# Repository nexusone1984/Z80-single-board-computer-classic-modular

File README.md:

# Z80-single-board-computer-classic-modular
CAD drawings and source code for projects using the Z80 single board computer

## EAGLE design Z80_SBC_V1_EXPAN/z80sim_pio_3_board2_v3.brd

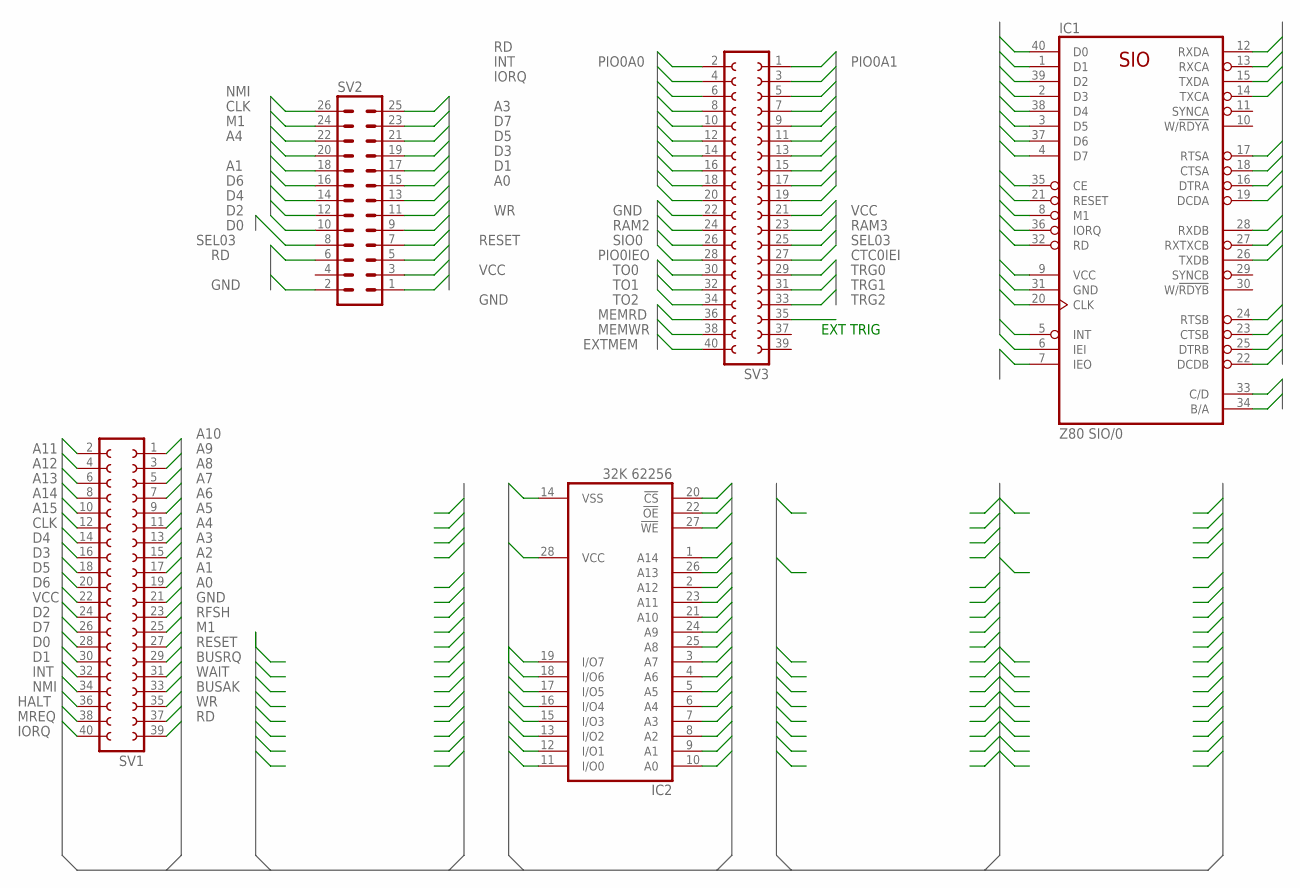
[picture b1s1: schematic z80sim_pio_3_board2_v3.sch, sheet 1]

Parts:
IC1: Z80 SIO/0; DIL40
IC2: 32K 62256; DIL28-6
SV1, SV3: FE20-2
SV2: MA13-2

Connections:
32K_SEL: IC2.20 (!CS); also elsewhere on the board
A0: IC1.34 (B/A), IC2.10 (A0), SV1.21, SV2.9
A1: IC1.33 (C/D), IC2.9 (A1), SV1.19, SV2.18
A2: IC2.8 (A2), SV1.17
A3: IC2.7 (A3), SV1.15, SV2.19
A4: IC2.6 (A4), SV1.13, SV2.20
A5: IC2.5 (A5), SV1.11
A6: IC2.4 (A6), SV1.9
A7: IC2.3 (A7), SV1.7
A8: IC2.25 (A8), SV1.5
A9: IC2.24 (A9), SV1.3
A10: IC2.21 (A10), SV1.1
A11: IC2.23 (A11), SV1.2
A12: IC2.2 (A12), SV1.4
A13: IC2.26 (A13), SV1.6
A14: IC2.1 (A14), SV1.8
A15: SV1.10
BUSAK: SV1.35
BUSRQ: SV1.31
CLK: IC1.20 (CLK), SV1.12, SV2.24
CTC0IEI: IC1.7 (IEO), SV3.27; also elsewhere on the board
CTSA: IC1.18 (CTSA)
CTSB: IC1.23 (CTSB)
D0: IC1.40 (D0), IC2.11 (I/O0), SV1.28, SV2.10
D1: IC1.1 (D1), IC2.12 (I/O1), SV1.30, SV2.11
D2: IC1.39 (D2), IC2.13 (I/O2), SV1.24, SV2.12
D3: IC1.2 (D3), IC2.15 (I/O3), SV1.16, SV2.13
D4: IC1.38 (D4), IC2.16 (I/O4), SV1.14, SV2.14
D5: IC1.3 (D5), IC2.17 (I/O5), SV1.18, SV2.15
D6: IC1.37 (D6), IC2.18 (I/O6), SV1.20, SV2.16
D7: IC1.4 (D7), IC2.19 (I/O7), SV1.26, SV2.17
DCDA: IC1.19 (DCDA)
DCDB: IC1.22 (DCDB)
DTRA: IC1.16 (DTRA)
DTRB: IC1.25 (DTRB)
EXTMEM: SV3.40
GND: IC1.31 (GND), IC2.14 (VSS), SV1.23, SV2.1, SV2.2, SV3.22; also elsewhere on the board
HALT: SV1.36
INT: IC1.5 (INT), SV1.32, SV2.23
IORQ: IC1.36 (IORQ), SV1.40, SV2.21; also elsewhere on the board
M1: IC1.8 (M1), SV1.27, SV2.22
MEMRD: IC2.22 (!OE), SV3.36
MEMWR: IC2.27 (!WE), SV3.38
MREQ: SV1.38
NMI: SV1.34, SV2.26
PIO0A0: SV3.2
PIO0A1: SV3.1
PIO0A2: SV3.4
PIO0A3: SV3.3
PIO0A4: SV3.6
PIO0A5: SV3.5
PIO0A6: SV3.8
PIO0A7: SV3.7
PIO0ARDY: SV3.10
PIO0ASTB: SV3.9
PIO0B0: SV3.12
PIO0B1: SV3.11
PIO0B2: SV3.14
PIO0B3: SV3.13
PIO0B4: SV3.16
PIO0B5: SV3.15
PIO0B6: SV3.18
PIO0B7: SV3.17
PIO0BRDY: SV3.20
PIO0BSTB: SV3.19
PIO0IEO: SV3.28
RAM2: SV3.24
RAM3: SV3.23
RD: IC1.32 (RD), SV1.39, SV2.6, SV2.25
RESET: IC1.21 (RESET), SV1.29, SV2.5
RFSH: SV1.25
RTSA: IC1.17 (RTSA)
RTSB: IC1.24 (RTSB)
RXCA: IC1.13 (RXCA)
RXDA: IC1.12 (RXDA)
RXDB: IC1.28 (RXDB)
RXTXCB: IC1.27 (RXTXCB)
SEL03: SV2.8, SV3.25
SIO0: IC1.35 (CE), SV3.26
TO0: SV3.30
TO1: SV3.32
TO2: SV3.34
TRG0: SV3.29
TRG1: SV3.31
TRG2: SV3.33
TXCA: IC1.14 (TXCA)
TXDA: IC1.15 (TXDA)
TXDB: IC1.26 (TXDB)
VCC: IC1.6 (IEI), IC1.9 (VCC), IC2.28 (VCC), SV1.22, SV2.3, SV3.21; also elsewhere on the board
WAIT: SV1.33
WR: SV1.37, SV2.7

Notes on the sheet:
EXT TRIG

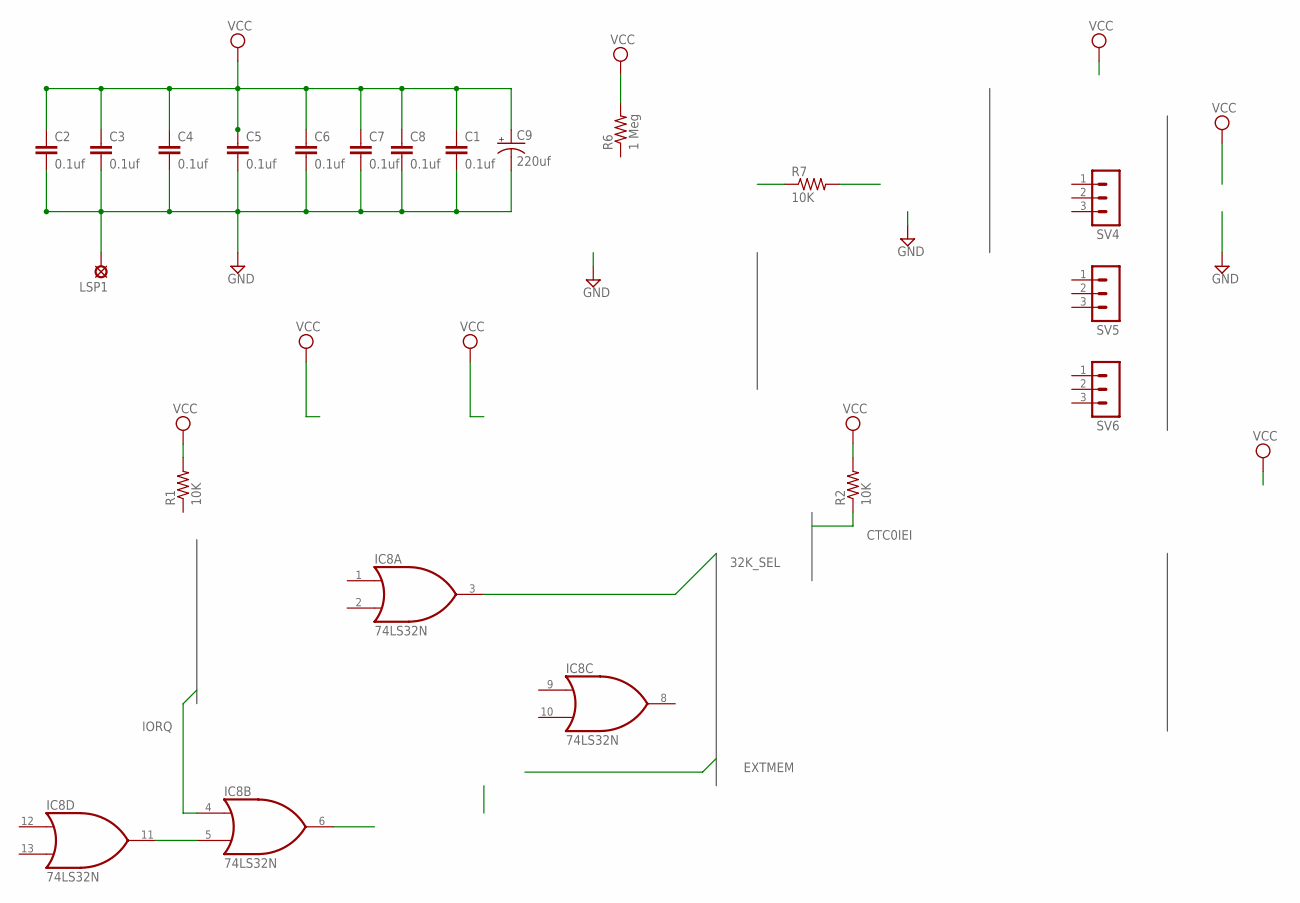
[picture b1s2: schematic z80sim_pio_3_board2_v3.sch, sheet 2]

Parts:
C1, C2, C3, C4, C5, C6, C7, C8: 0.1uf; C5B3
C9: 220uf; E3,5-10
IC8: 74LS32N; DIL14
LSP1: LSP13
R1, R2, R7: 10K; 0204/7
R6: 1 Meg; 0204/7
SV4, SV5, SV6: MA03-1

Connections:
32K_SEL: IC8.3 (O); also elsewhere on the board
CTC0IEI: R2.1; also elsewhere on the board
GND: C1.2, C2.2, C3.2, C4.2, C5.2, C6.2, C7.2, C8.2, C9.-, IC8.7 (GND), LSP1.MP; also elsewhere on the board
IORQ: IC8.4 (I0); also elsewhere on the board
unnamed: IC8.5 (I1), IC8.11 (O)
VCC: C1.1, C2.1, C3.1, C4.1, C5.1, C6.1, C7.1, C8.1, C9.+, IC8.14 (VCC), R1.2, R2.2, R6.2; also elsewhere on the board

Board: 2 copper layers, 23 parts (0 on the bottom side), 40 nets, no tracks yet.

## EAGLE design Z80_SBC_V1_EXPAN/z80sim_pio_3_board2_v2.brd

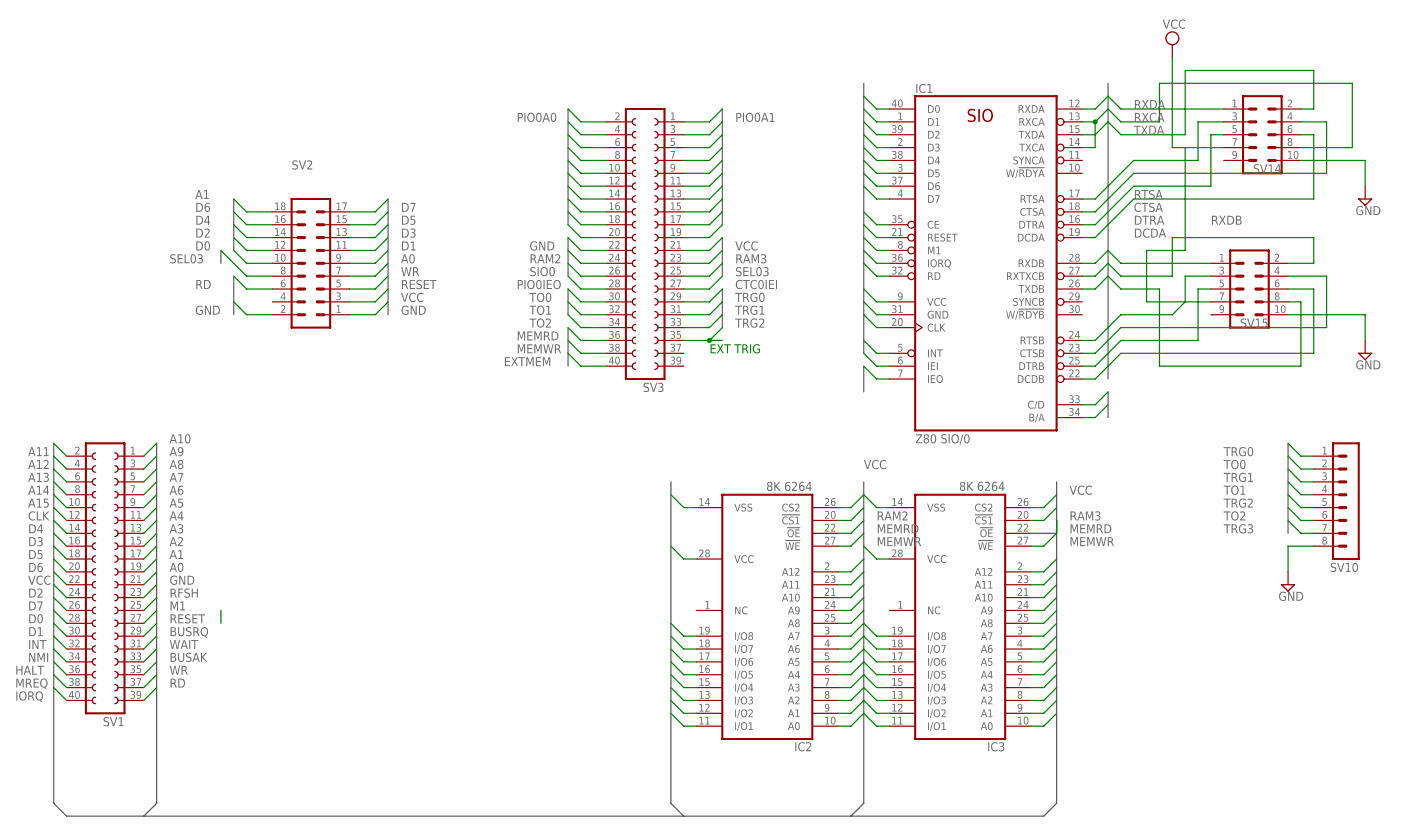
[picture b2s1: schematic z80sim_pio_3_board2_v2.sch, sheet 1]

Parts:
IC1: Z80 SIO/0; DIL40
IC2, IC3: 8K 6264; DIL28-6
SV1, SV3: FE20-2
SV2: MA09-2
SV10: MA08-1
SV14, SV15: MA05-2

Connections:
A0: IC1.34 (B/A), IC2.10 (A0), IC3.10 (A0), SV1.21, SV2.9
A1: IC1.33 (C/D), IC2.9 (A1), IC3.9 (A1), SV1.19, SV2.18
A2: IC2.8 (A2), IC3.8 (A2), SV1.17
A3: IC2.7 (A3), IC3.7 (A3), SV1.15
A4: IC2.6 (A4), IC3.6 (A4), SV1.13
A5: IC2.5 (A5), IC3.5 (A5), SV1.11
A6: IC2.4 (A6), IC3.4 (A6), SV1.9
A7: IC2.3 (A7), IC3.3 (A7), SV1.7
A8: IC2.25 (A8), IC3.25 (A8), SV1.5
A9: IC2.24 (A9), IC3.24 (A9), SV1.3
A10: IC2.21 (A10), IC3.21 (A10), SV1.1
A11: IC2.23 (A11), IC3.23 (A11), SV1.2
A12: IC2.2 (A12), IC3.2 (A12), SV1.4
A13: SV1.6
A14: SV1.8
A15: SV1.10
BUSAK: SV1.35
BUSRQ: SV1.31
CLK: IC1.20 (CLK), SV1.12
CTC0IEI: IC1.7 (IEO), SV3.27; also elsewhere on the board
CTSA: IC1.18 (CTSA), SV14.4
CTSB: IC1.23 (CTSB), SV15.4
D0: IC1.40 (D0), IC2.11 (I/O1), IC3.11 (I/O1), SV1.28, SV2.10
D1: IC1.1 (D1), IC2.12 (I/O2), IC3.12 (I/O2), SV1.30, SV2.11
D2: IC1.39 (D2), IC2.13 (I/O3), IC3.13 (I/O3), SV1.24, SV2.12
D3: IC1.2 (D3), IC2.15 (I/O4), IC3.15 (I/O4), SV1.16, SV2.13
D4: IC1.38 (D4), IC2.16 (I/O5), IC3.16 (I/O5), SV1.14, SV2.14
D5: IC1.3 (D5), IC2.17 (I/O6), IC3.17 (I/O6), SV1.18, SV2.15
D6: IC1.37 (D6), IC2.18 (I/O7), IC3.18 (I/O7), SV1.20, SV2.16
D7: IC1.4 (D7), IC2.19 (I/O8), IC3.19 (I/O8), SV1.26, SV2.17
DCDA: IC1.19 (DCDA), SV14.6
DCDB: IC1.22 (DCDB), SV15.6
DTRA: IC1.16 (DTRA), SV14.5
DTRB: IC1.25 (DTRB), SV15.5
EXTMEM: SV3.40
GND: IC1.31 (GND), IC2.14 (VSS), IC3.14 (VSS), SV1.23, SV2.1, SV2.2, SV3.22, SV10.8, SV14.10, SV15.10; also elsewhere on the board
HALT: SV1.36
INT: IC1.5 (INT), SV1.32
IORQ: IC1.36 (IORQ), SV1.40
M1: IC1.8 (M1), SV1.27
MEMRD: IC2.22 (!OE), IC3.22 (!OE), SV3.36
MEMWR: IC2.27 (!WE), IC3.27 (!WE), SV3.38
MREQ: SV1.38
NMI: SV1.34
PIO0A0: SV3.2; also elsewhere on the board
PIO0A1: SV3.1; also elsewhere on the board
PIO0A2: SV3.4; also elsewhere on the board
PIO0A3: SV3.3; also elsewhere on the board
PIO0A4: SV3.6; also elsewhere on the board
PIO0A5: SV3.5; also elsewhere on the board
PIO0A6: SV3.8; also elsewhere on the board
PIO0A7: SV3.7; also elsewhere on the board
PIO0ARDY: SV3.10; also elsewhere on the board
PIO0ASTB: SV3.9; also elsewhere on the board
PIO0B0: SV3.12; also elsewhere on the board
PIO0B1: SV3.11; also elsewhere on the board
PIO0B2: SV3.14; also elsewhere on the board
PIO0B3: SV3.13; also elsewhere on the board
PIO0B4: SV3.16; also elsewhere on the board
PIO0B5: SV3.15; also elsewhere on the board
PIO0B6: SV3.18; also elsewhere on the board
PIO0B7: SV3.17; also elsewhere on the board
PIO0BRDY: SV3.20; also elsewhere on the board
PIO0BSTB: SV3.19; also elsewhere on the board
PIO0IEO: SV3.28
RAM2: IC2.20 (!CS1), SV3.24
RAM3: IC3.20 (!CS1), SV3.23
RD: IC1.32 (RD), SV1.39, SV2.6
RESET: IC1.21 (RESET), SV1.29, SV2.5
RFSH: SV1.25
RTSA: IC1.17 (RTSA), SV14.3
RTSB: IC1.24 (RTSB), SV15.3
RXCA: IC1.13 (RXCA), IC1.14 (TXCA), SV14.8; also elsewhere on the board
RXDA: IC1.12 (RXDA), SV14.1
RXDB: IC1.28 (RXDB), SV15.1
RXTXCB: IC1.27 (RXTXCB), SV15.8; also elsewhere on the board
SEL03: SV2.8, SV3.25
SIO0: IC1.35 (CE), SV3.26
TO0: SV3.30, SV10.2; also elsewhere on the board
TO1: SV3.32, SV10.4; also elsewhere on the board
TO2: SV3.34, SV10.6
TRG0: SV3.29, SV10.1
TRG1: SV3.31, SV10.3
TRG2: SV3.33, SV10.5
TRG3: SV3.35, SV10.7
TXDA: IC1.15 (TXDA), SV14.2
TXDB: IC1.26 (TXDB), SV15.2
VCC: IC1.6 (IEI), IC1.9 (VCC), IC2.26 (CS2), IC2.28 (VCC), IC3.26 (CS2), IC3.28 (VCC), SV1.22, SV2.3, SV3.21, SV14.7, SV15.7; also elsewhere on the board
WAIT: SV1.33
WR: SV1.37, SV2.7

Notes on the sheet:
EXT TRIG

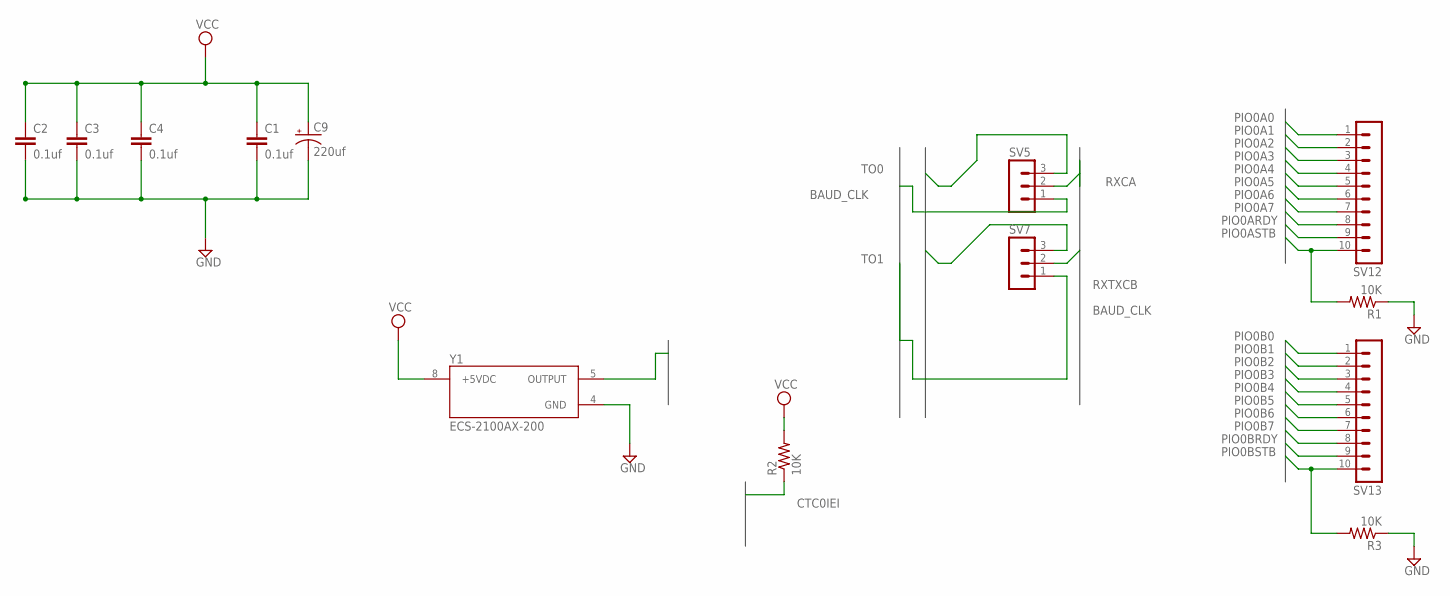
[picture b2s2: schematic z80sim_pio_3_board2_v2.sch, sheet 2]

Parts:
C1, C2, C3, C4: 0.1uf; C5B3
C9: 220uf; E3,5-10
R1, R2, R3: 10K; 0204/7
SV5, SV7: MA03-1
SV12, SV13: MA10-1
Y1: ECS-2100AX-200

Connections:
BAUD_CLK: SV5.1, SV7.1, Y1.5 (OUTPUT)
CTC0IEI: R2.1; also elsewhere on the board
GND: C1.2, C2.2, C3.2, C4.2, C9.-, R1.1, R3.1, Y1.4 (GND); also elsewhere on the board
PIO0A0: SV12.1; also elsewhere on the board
PIO0A1: SV12.2; also elsewhere on the board
PIO0A2: SV12.3; also elsewhere on the board
PIO0A3: SV12.4; also elsewhere on the board
PIO0A4: SV12.5; also elsewhere on the board
PIO0A5: SV12.6; also elsewhere on the board
PIO0A6: SV12.7; also elsewhere on the board
PIO0A7: SV12.8; also elsewhere on the board
PIO0ARDY: SV12.9; also elsewhere on the board
PIO0ASTB: R1.2, SV12.10; also elsewhere on the board
PIO0B0: SV13.1; also elsewhere on the board
PIO0B1: SV13.2; also elsewhere on the board
PIO0B2: SV13.3; also elsewhere on the board
PIO0B3: SV13.4; also elsewhere on the board
PIO0B4: SV13.5; also elsewhere on the board
PIO0B5: SV13.6; also elsewhere on the board
PIO0B6: SV13.7; also elsewhere on the board
PIO0B7: SV13.8; also elsewhere on the board
PIO0BRDY: SV13.9; also elsewhere on the board
PIO0BSTB: R3.2, SV13.10; also elsewhere on the board
RXCA: SV5.2; also elsewhere on the board
RXTXCB: SV7.2; also elsewhere on the board
TO0: SV5.3; also elsewhere on the board
TO1: SV7.3; also elsewhere on the board
VCC: C1.1, C2.1, C3.1, C4.1, C9.+, R2.2, Y1.8 (+5VDC); also elsewhere on the board

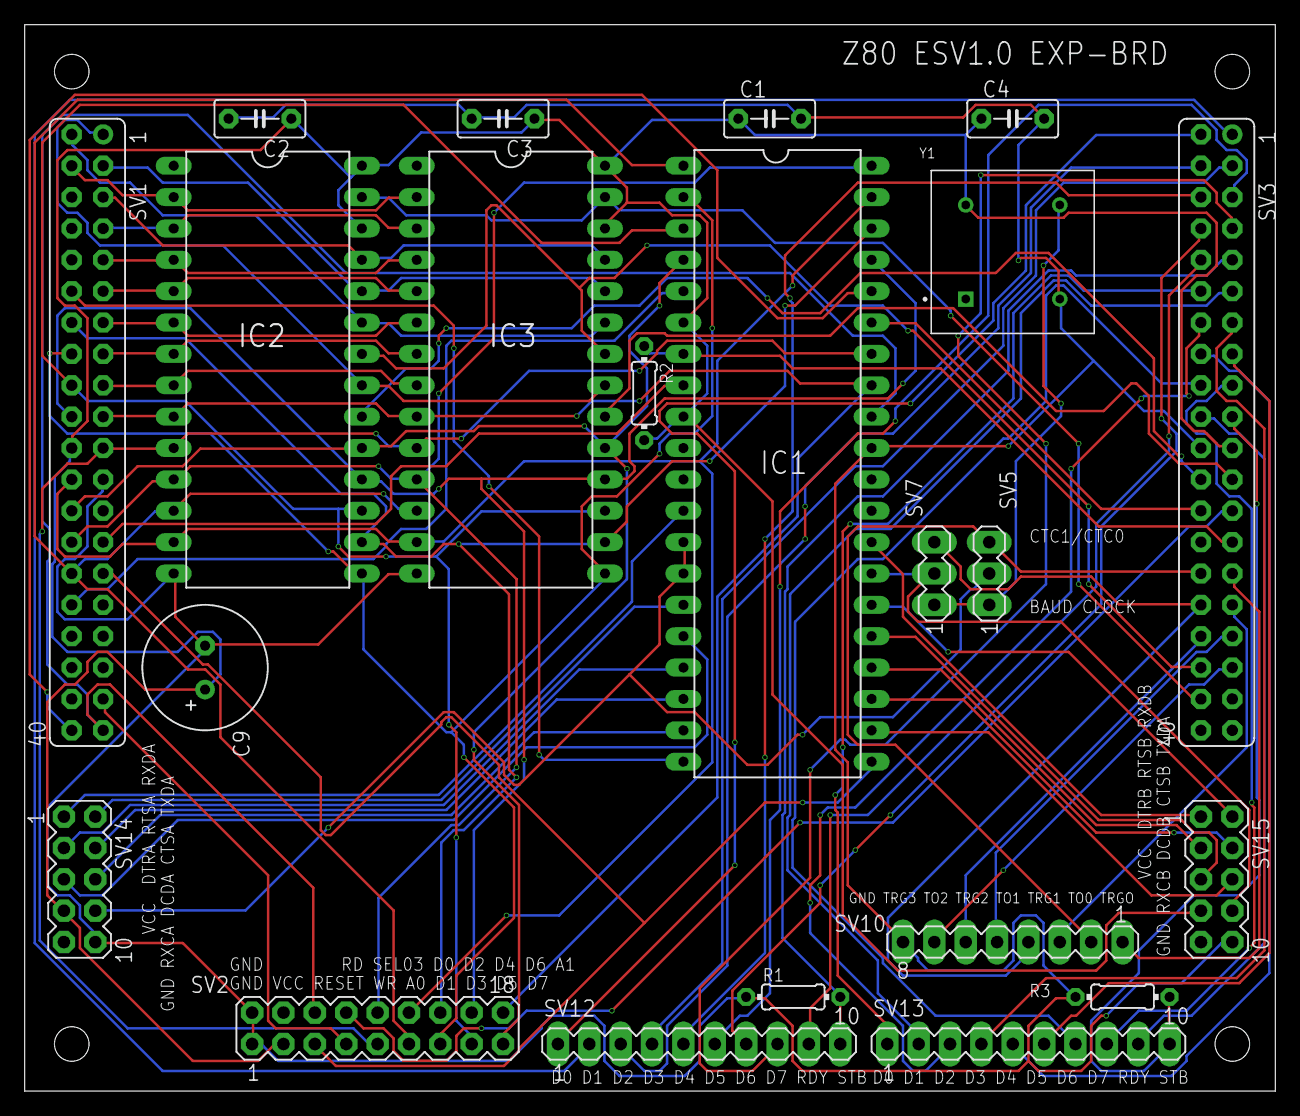
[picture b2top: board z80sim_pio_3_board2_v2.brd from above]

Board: 2 copper layers, 101.3 x 86.3 mm, 22 parts (0 on the bottom side), 79 nets.

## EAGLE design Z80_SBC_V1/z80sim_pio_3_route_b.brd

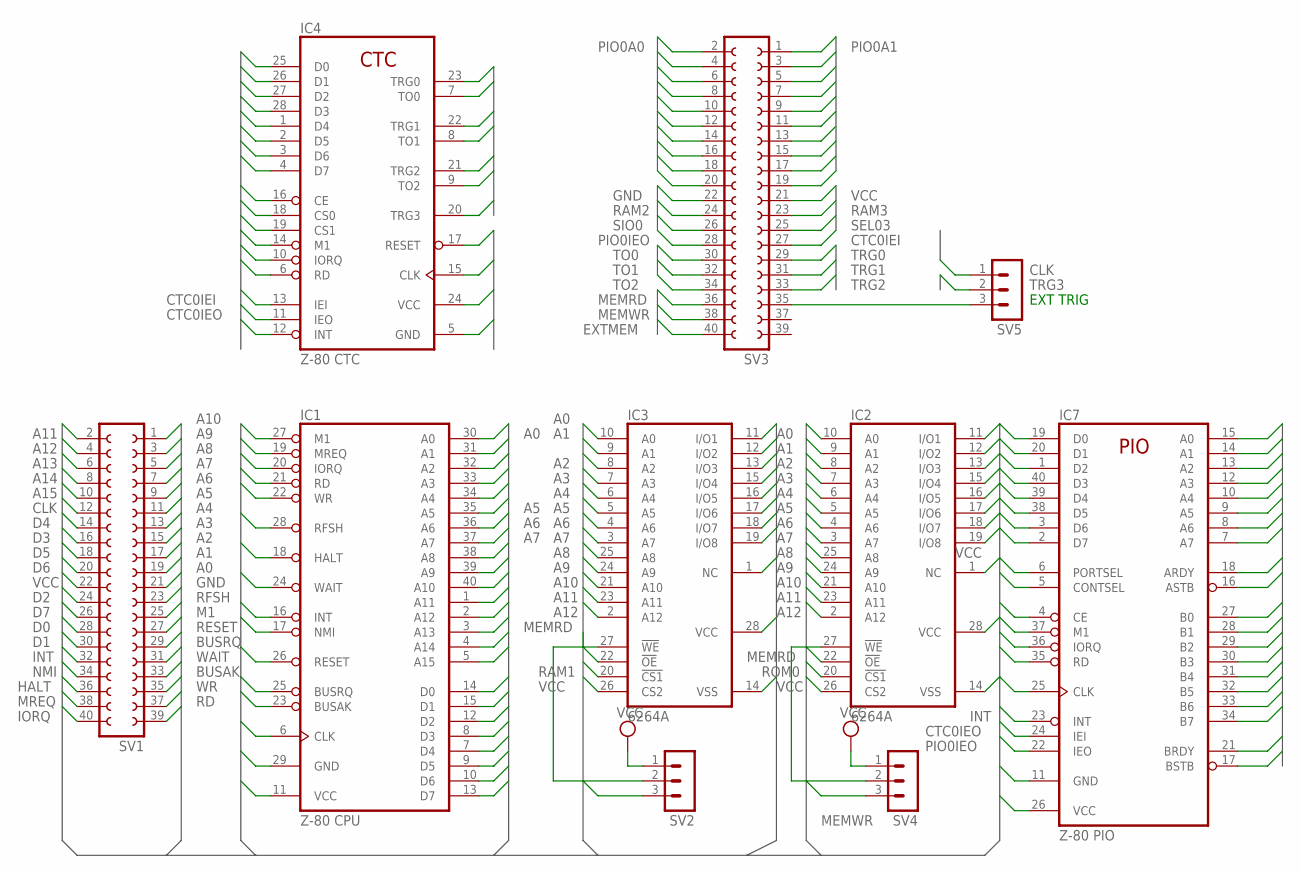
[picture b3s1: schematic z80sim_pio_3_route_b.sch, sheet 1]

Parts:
IC1: Z-80 CPU; DIL40
IC2, IC3: 6264A; DIL28-6
IC4: Z-80 CTC; DIL28
IC7: Z-80 PIO; DIL40
SV1, SV3: FE20-2
SV2, SV4, SV5: MA03-1

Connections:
A0: IC1.30 (A0), IC2.10 (A0), IC3.10 (A0), IC4.18 (CS0), IC7.6 (PORTSEL), SV1.21
A1: IC1.31 (A1), IC2.9 (A1), IC3.9 (A1), IC4.19 (CS1), IC7.5 (CONTSEL), SV1.19
A2: IC1.32 (A2), IC2.8 (A2), IC3.8 (A2), SV1.17
A3: IC1.33 (A3), IC2.7 (A3), IC3.7 (A3), SV1.15
A4: IC1.34 (A4), IC2.6 (A4), IC3.6 (A4), SV1.13
A5: IC1.35 (A5), IC2.5 (A5), IC3.5 (A5), SV1.11; also elsewhere on the board
A6: IC1.36 (A6), IC2.4 (A6), IC3.4 (A6), SV1.9; also elsewhere on the board
A7: IC1.37 (A7), IC2.3 (A7), IC3.3 (A7), SV1.7; also elsewhere on the board
A8: IC1.38 (A8), IC2.25 (A8), IC3.25 (A8), SV1.5
A9: IC1.39 (A9), IC2.24 (A9), IC3.24 (A9), SV1.3
A10: IC1.40 (A10), IC2.21 (A10), IC3.21 (A10), SV1.1
A11: IC1.1 (A11), IC2.23 (A11), IC3.23 (A11), SV1.2
A12: IC1.2 (A12), IC2.2 (A12), IC3.2 (A12), SV1.4
A13: IC1.3 (A13), SV1.6; also elsewhere on the board
A14: IC1.4 (A14), SV1.8; also elsewhere on the board
A15: IC1.5 (A15), SV1.10; also elsewhere on the board
BUSAK: IC1.23 (BUSAK), SV1.35
BUSRQ: IC1.25 (BUSRQ), SV1.31; also elsewhere on the board
CLK: IC1.6 (CLK), IC4.15 (CLK), IC7.25 (CLK), SV1.12, SV5.1; also elsewhere on the board
CTC0: IC4.16 (CE); also elsewhere on the board
CTC0IEI: IC4.13 (IEI), SV3.27; also elsewhere on the board
CTC0IEO: IC4.11 (IEO), IC7.24 (IEI)
D0: IC1.14 (D0), IC2.11 (I/O1), IC3.11 (I/O1), IC4.25 (D0), IC7.19 (D0), SV1.28
D1: IC1.15 (D1), IC2.12 (I/O2), IC3.12 (I/O2), IC4.26 (D1), IC7.20 (D1), SV1.30
D2: IC1.12 (D2), IC2.13 (I/O3), IC3.13 (I/O3), IC4.27 (D2), IC7.1 (D2), SV1.24
D3: IC1.8 (D3), IC2.15 (I/O4), IC3.15 (I/O4), IC4.28 (D3), IC7.40 (D3), SV1.16
D4: IC1.7 (D4), IC2.16 (I/O5), IC3.16 (I/O5), IC4.1 (D4), IC7.39 (D4), SV1.14
D5: IC1.9 (D5), IC2.17 (I/O6), IC3.17 (I/O6), IC4.2 (D5), IC7.38 (D5), SV1.18
D6: IC1.10 (D6), IC2.18 (I/O7), IC3.18 (I/O7), IC4.3 (D6), IC7.3 (D6), SV1.20
D7: IC1.13 (D7), IC2.19 (I/O8), IC3.19 (I/O8), IC4.4 (D7), IC7.2 (D7), SV1.26
EXTMEM: SV3.40; also elsewhere on the board
GND: IC1.29 (GND), IC2.14 (VSS), IC3.14 (VSS), IC4.5 (GND), IC7.11 (GND), SV1.23, SV3.22; also elsewhere on the board
HALT: IC1.18 (HALT), SV1.36
INT: IC1.16 (INT), IC4.12 (INT), IC7.23 (INT), SV1.32; also elsewhere on the board
IORQ: IC1.20 (IORQ), IC4.10 (IORQ), IC7.36 (IORQ), SV1.40; also elsewhere on the board
M1: IC1.27 (M1), IC4.14 (M1), IC7.37 (M1), SV1.27
MEMRD: IC2.22 (!OE), IC3.22 (!OE), SV3.36; also elsewhere on the board
MEMWR: SV2.3, SV3.38, SV4.3; also elsewhere on the board
MREQ: IC1.19 (MREQ), SV1.38; also elsewhere on the board
unnamed: IC2.27 (!WE), SV4.2
unnamed: SV3.35, SV5.3
unnamed: IC3.27 (!WE), SV2.2
NMI: IC1.17 (NMI), SV1.34; also elsewhere on the board
PIO0: IC7.4 (CE); also elsewhere on the board
PIO0A0: IC7.15 (A0), SV3.2
PIO0A1: IC7.14 (A1), SV3.1
PIO0A2: IC7.13 (A2), SV3.4
PIO0A3: IC7.12 (A3), SV3.3
PIO0A4: IC7.10 (A4), SV3.6
PIO0A5: IC7.9 (A5), SV3.5
PIO0A6: IC7.8 (A6), SV3.8
PIO0A7: IC7.7 (A7), SV3.7
PIO0ARDY: IC7.18 (ARDY), SV3.10
PIO0ASTB: IC7.16 (ASTB), SV3.9
PIO0B0: IC7.27 (B0), SV3.12
PIO0B1: IC7.28 (B1), SV3.11
PIO0B2: IC7.29 (B2), SV3.14
PIO0B3: IC7.30 (B3), SV3.13
PIO0B4: IC7.31 (B4), SV3.16
PIO0B5: IC7.32 (B5), SV3.15
PIO0B6: IC7.33 (B6), SV3.18
PIO0B7: IC7.34 (B7), SV3.17
PIO0BRDY: IC7.21 (BRDY), SV3.20
PIO0BSTB: IC7.17 (BSTB), SV3.19
PIO0IEO: IC7.22 (IEO), SV3.28
RAM1: IC3.20 (!CS1); also elsewhere on the board
RAM2: SV3.24; also elsewhere on the board
RAM3: SV3.23; also elsewhere on the board
RD: IC1.21 (RD), IC4.6 (RD), IC7.35 (RD), SV1.39; also elsewhere on the board
RESET: IC1.26 (RESET), IC4.17 (RESET), SV1.29; also elsewhere on the board
RFSH: IC1.28 (RFSH), SV1.25
ROM0: IC2.20 (!CS1); also elsewhere on the board
SEL03: SV3.25; also elsewhere on the board
SIO0: SV3.26; also elsewhere on the board
TO0: IC4.7 (TO0), SV3.30
TO1: IC4.8 (TO1), SV3.32
TO2: IC4.9 (TO2), SV3.34
TRG0: IC4.23 (TRG0), SV3.29
TRG1: IC4.22 (TRG1), SV3.31
TRG2: IC4.21 (TRG2), SV3.33
TRG3: IC4.20 (TRG3), SV5.2
VCC: IC1.11 (VCC), IC2.1 (NC), IC2.26 (CS2), IC2.28 (VCC), IC3.1 (NC), IC3.26 (CS2), IC3.28 (VCC), IC4.24 (VCC), IC7.26 (VCC), SV1.22, SV2.1, SV3.21, SV4.1; also elsewhere on the board
WAIT: IC1.24 (WAIT), SV1.33; also elsewhere on the board
WR: IC1.22 (WR), SV1.37; also elsewhere on the board

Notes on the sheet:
EXT TRIG

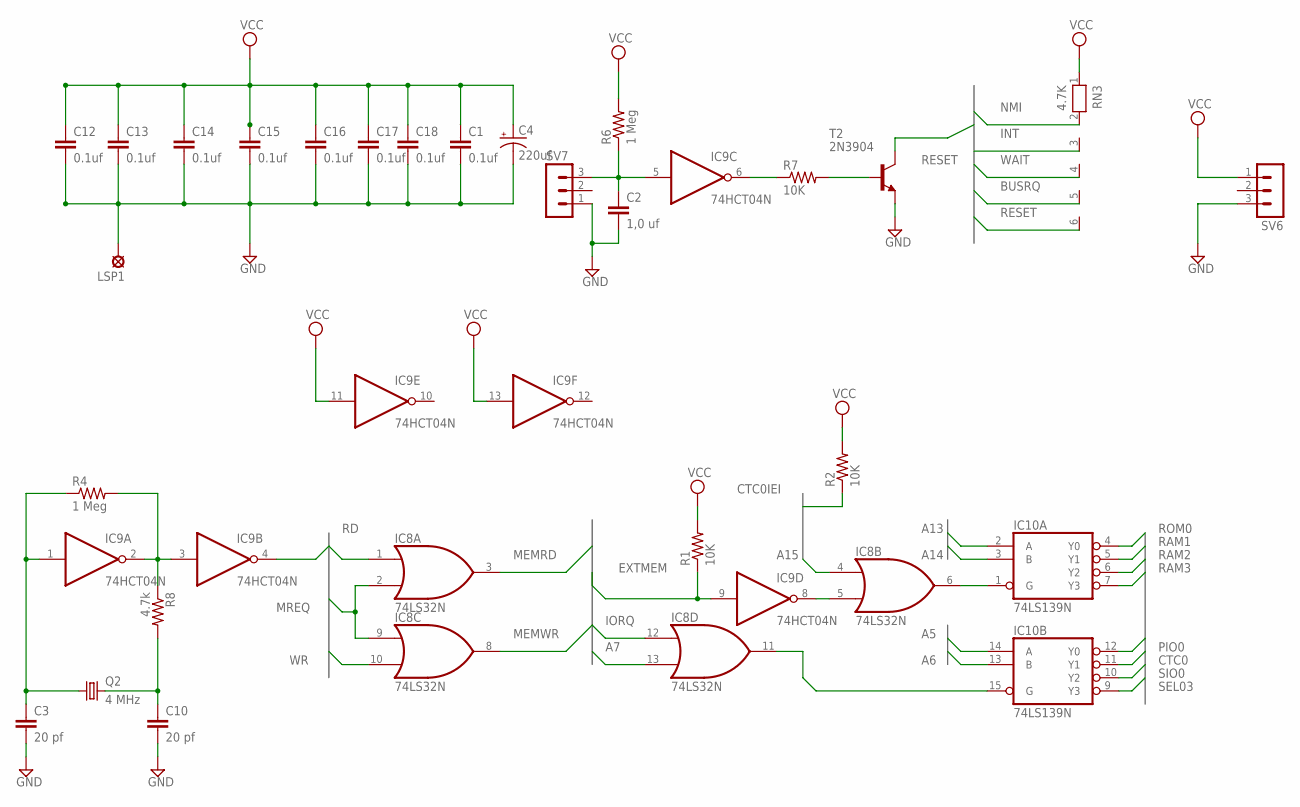
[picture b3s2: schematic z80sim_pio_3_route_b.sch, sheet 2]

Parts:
C1, C12, C13, C14, C15, C16, C17, C18: 0.1uf; C5B3
C2: 1,0 uf; C5B3
C3, C10: 20 pf; C2.5-5
C4: 220uf; E3,5-10
IC8: 74LS32N; DIL14
IC9: 74HCT04N; DIL14
IC10: 74LS139N; DIL16
LSP1: LSP13
Q2: 4 MHz; HC49/S
R1, R2, R7: 10K; 0204/7
R4, R6: 1 Meg; 0204/7
R8: 4.7k; 0204/7
RN3: 4.7K; RN-6
SV6, SV7: MA03-1
T2: 2N3904; TO92

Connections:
A5: IC10.14 (A); also elsewhere on the board
A6: IC10.13 (B); also elsewhere on the board
A7: IC8.13 (I1); also elsewhere on the board
A13: IC10.2 (A); also elsewhere on the board
A14: IC10.3 (B); also elsewhere on the board
A15: IC8.4 (I0); also elsewhere on the board
BUSRQ: RN3.5; also elsewhere on the board
CLK: IC9.4 (O); also elsewhere on the board
CTC0: IC10.11 (Y1); also elsewhere on the board
CTC0IEI: R2.1; also elsewhere on the board
EXTMEM: IC9.9 (I), R1.1; also elsewhere on the board
GND: C1.2, C2.2, C3.2, C4.-, C10.2, C12.2, C13.2, C14.2, C15.2, C16.2, C17.2, C18.2, IC8.7 (GND), IC9.7 (GND), IC10.8 (GND), LSP1.MP, SV6.3, SV7.1, T2.3 (E); also elsewhere on the board
INT: RN3.2; also elsewhere on the board
IORQ: IC8.12 (I0); also elsewhere on the board
MEMRD: IC8.3 (O); also elsewhere on the board
MEMWR: IC8.8 (O); also elsewhere on the board
MREQ: IC8.2 (I1), IC8.9 (I0); also elsewhere on the board
unnamed: IC8.6 (O), IC10.1 (G)
unnamed: IC8.5 (I1), IC9.8 (O)
unnamed: C10.1, Q2.2, R8.2
unnamed: C3.1, IC9.1 (I), Q2.1, R4.1
unnamed: IC9.2 (O), IC9.3 (I), R4.2, R8.1
unnamed: IC9.6 (O), R7.1
unnamed: C2.1, IC9.5 (I), R6.1, SV7.3
unnamed: R7.2, T2.2 (B)
unnamed: IC8.11 (O), IC10.15 (G)
NMI: RN3.3; also elsewhere on the board
PIO0: IC10.12 (Y0); also elsewhere on the board
RAM1: IC10.5 (Y1); also elsewhere on the board
RAM2: IC10.6 (Y2); also elsewhere on the board
RAM3: IC10.7 (Y3); also elsewhere on the board
RD: IC8.1 (I0); also elsewhere on the board
RESET: RN3.6, T2.1 (C); also elsewhere on the board
ROM0: IC10.4 (Y0); also elsewhere on the board
SEL03: IC10.9 (Y3); also elsewhere on the board
SIO0: IC10.10 (Y2); also elsewhere on the board
VCC: C1.1, C4.+, C12.1, C13.1, C14.1, C15.1, C16.1, C17.1, C18.1, IC8.14 (VCC), IC9.11 (I), IC9.13 (I), IC9.14 (VCC), IC10.16 (VCC), R1.2, R2.2, R6.2, RN3.1, SV6.1; also elsewhere on the board
WAIT: RN3.4; also elsewhere on the board
WR: IC8.10 (I1); also elsewhere on the board

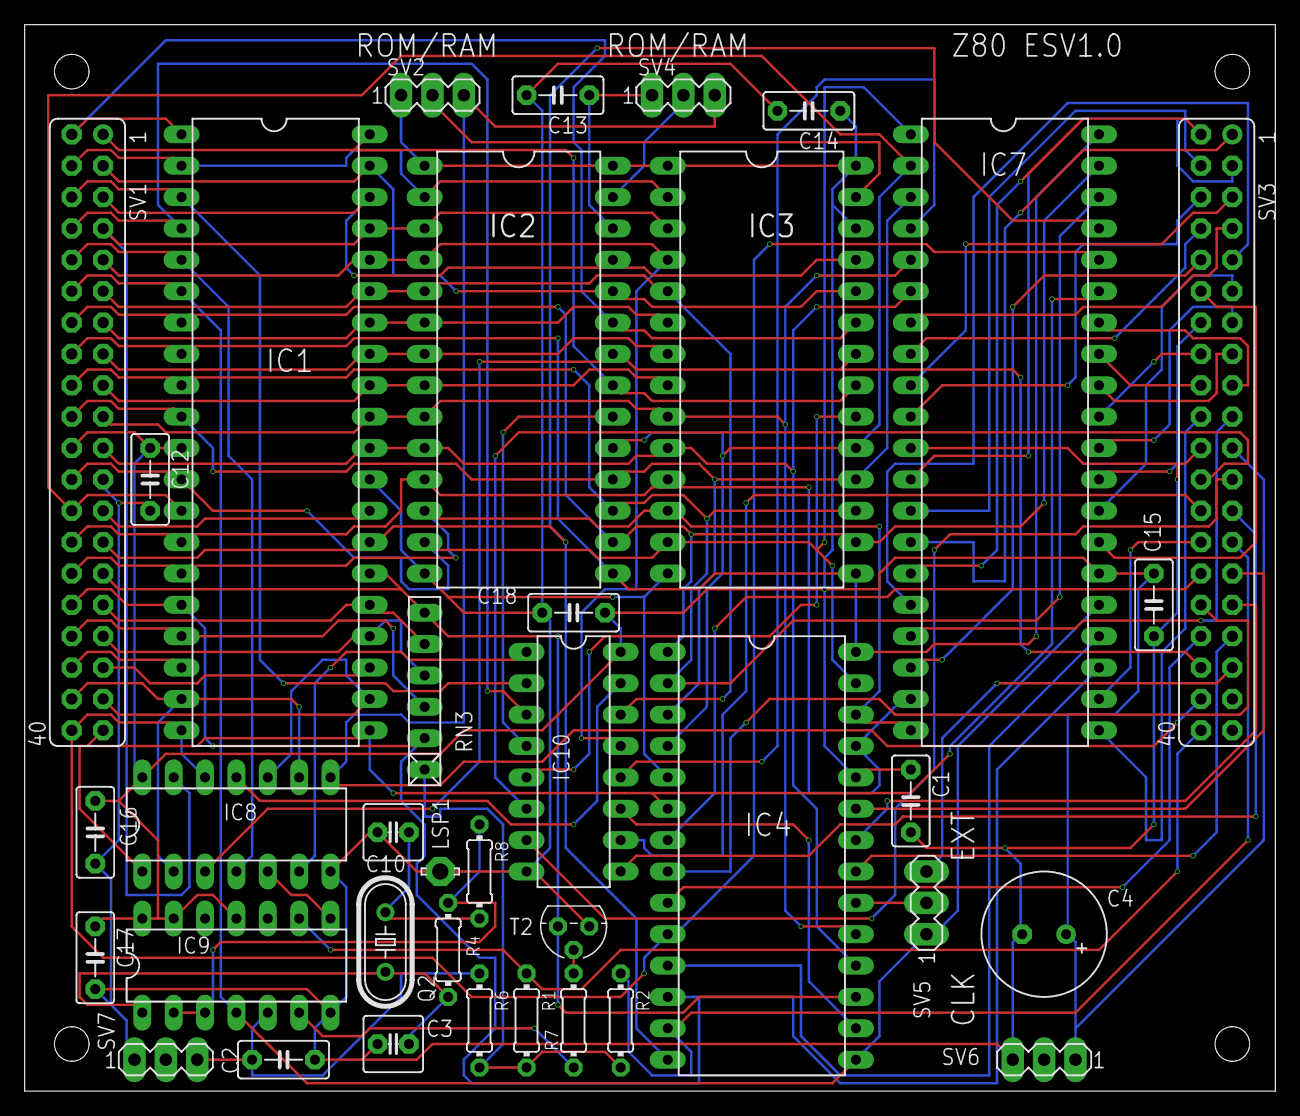
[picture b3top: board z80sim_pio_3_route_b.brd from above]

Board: 2 copper layers, 101.3 x 86.3 mm, 37 parts (0 on the bottom side), 93 nets.
